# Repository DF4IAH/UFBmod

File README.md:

# UFBmod
Ultra-Fine-Business Modulation - Trying a new data modulation to compete with LoRa (R)

## Topics
UFMmod is intented to be a digital Spread Spectrum Modulation for data transfer with Low Power and High Range performance. It is non-chirp based, instead it uses Pseudo-Noise coding sequence.

## The frequencies to be used by UFMmod

### Europe
* 868 MHz ISM band (125 kHz bandwidth).
* 433 MHz band (3 kHz bandwidth).

### USA, Australia, Asia, Africa, Pacific region ...
* sorry, not defined yet.

## Directory structure

### DOCS
* Ideas and concepts of the modulation and realization for an data packet transceiver.
* Datasheets of the used parts.

### HW
* CAD/Eagle schematics and PCB layout
* Libraries
* CAM files

### FPGA
* XILINX Artix-7 configuration files with its Verilog source code.

### SW
* Software used by the FPGA internal soft processor. (not yet defined)
* Software used by an STM32L4xx MCU. (not yet defined)

<EOF>

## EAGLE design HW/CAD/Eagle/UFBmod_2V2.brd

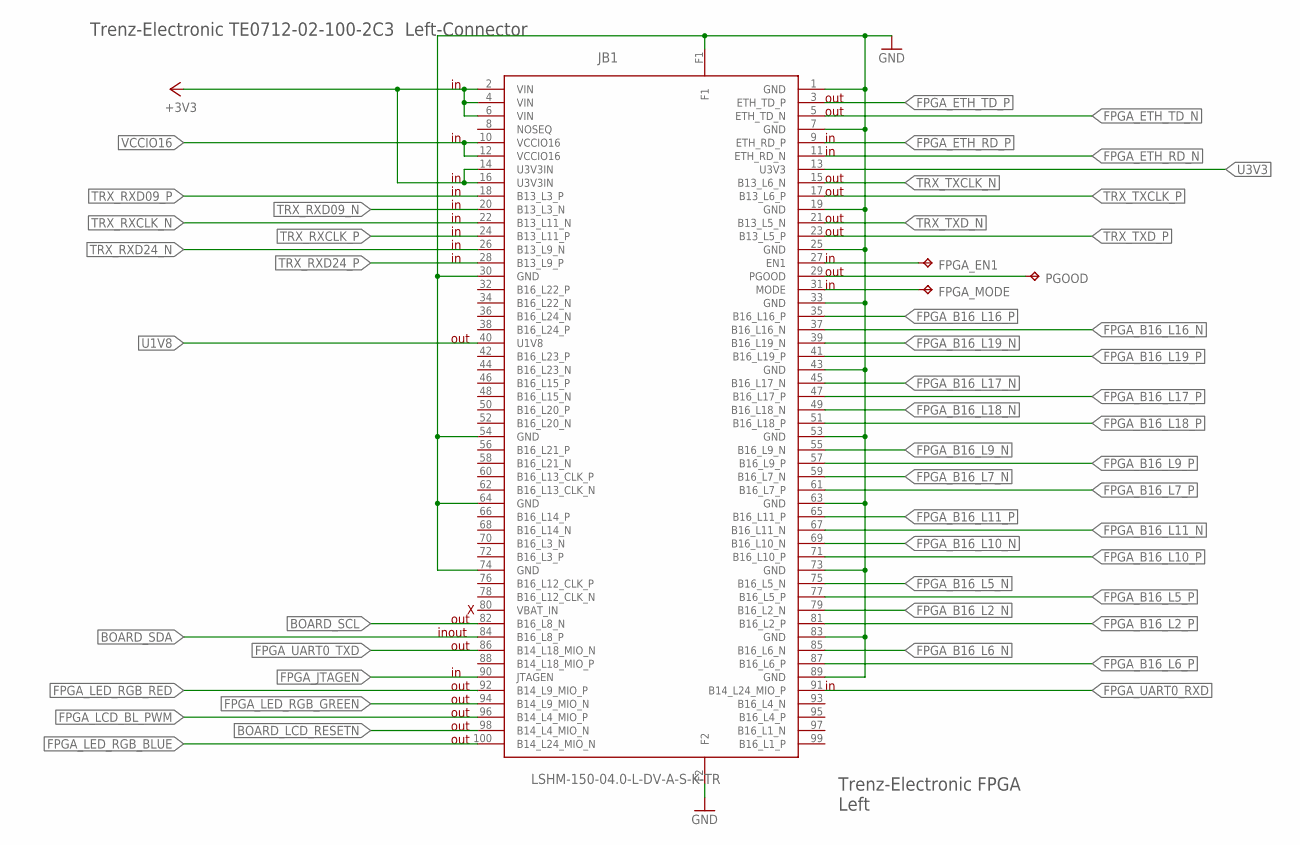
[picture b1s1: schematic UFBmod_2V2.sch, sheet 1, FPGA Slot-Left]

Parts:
FPGA_EN1: TPB1,27; B1,27
FPGA_MODE: TPB1,27; B1,27
JB1: LSHM-150-04.0-L-DV-A-S-K-TR; SAMTEC_LSHM-150-DV
PGOOD: TPB1,27; B1,27

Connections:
+3V3: JB1.2 (VIN), JB1.4 (VIN), JB1.6 (VIN), JB1.14 (U3V3IN), JB1.16 (U3V3IN); also elsewhere on the board
BOARD_LCD_RESETN: JB1.98 (B14_L4_MIO_N); also elsewhere on the board
BOARD_SCL: JB1.82 (B16_L8_N); also elsewhere on the board
BOARD_SDA: JB1.84 (B16_L8_P); also elsewhere on the board
FPGA_B16_L2_N: JB1.79 (B16_L2_N)
FPGA_B16_L2_P: JB1.81 (B16_L2_P)
FPGA_B16_L5_N: JB1.75 (B16_L5_N)
FPGA_B16_L5_P: JB1.77 (B16_L5_P)
FPGA_B16_L6_N: JB1.85 (B16_L6_N)
FPGA_B16_L6_P: JB1.87 (B16_L6_P)
FPGA_B16_L7_N: JB1.59 (B16_L7_N); also elsewhere on the board
FPGA_B16_L7_P: JB1.61 (B16_L7_P); also elsewhere on the board
FPGA_B16_L9_N: JB1.55 (B16_L9_N); also elsewhere on the board
FPGA_B16_L9_P: JB1.57 (B16_L9_P); also elsewhere on the board
FPGA_B16_L10_N: JB1.69 (B16_L10_N)
FPGA_B16_L10_P: JB1.71 (B16_L10_P)
FPGA_B16_L11_N: JB1.67 (B16_L11_N); also elsewhere on the board
FPGA_B16_L11_P: JB1.65 (B16_L11_P); also elsewhere on the board
FPGA_B16_L16_N: JB1.37 (B16_L16_N); also elsewhere on the board
FPGA_B16_L16_P: JB1.35 (B16_L16_P); also elsewhere on the board
FPGA_B16_L17_N: JB1.45 (B16_L17_N); also elsewhere on the board
FPGA_B16_L17_P: JB1.47 (B16_L17_P); also elsewhere on the board
FPGA_B16_L18_N: JB1.49 (B16_L18_N); also elsewhere on the board
FPGA_B16_L18_P: JB1.51 (B16_L18_P); also elsewhere on the board
FPGA_B16_L19_N: JB1.39 (B16_L19_N); also elsewhere on the board
FPGA_B16_L19_P: JB1.41 (B16_L19_P); also elsewhere on the board
FPGA_EN1: FPGA_EN1.TP, JB1.27 (EN1)
FPGA_ETH_RD_N: JB1.11 (ETH_RD_N); also elsewhere on the board
FPGA_ETH_RD_P: JB1.9 (ETH_RD_P); also elsewhere on the board
FPGA_ETH_TD_N: JB1.5 (ETH_TD_N); also elsewhere on the board
FPGA_ETH_TD_P: JB1.3 (ETH_TD_P); also elsewhere on the board
FPGA_JTAGEN: JB1.90 (JTAGEN); also elsewhere on the board
FPGA_LCD_BL_PWM: JB1.96 (B14_L4_MIO_P); also elsewhere on the board
FPGA_LED_RGB_BLUE: JB1.100 (B14_L24_MIO_N); also elsewhere on the board
FPGA_LED_RGB_GREEN: JB1.94 (B14_L9_MIO_N); also elsewhere on the board
FPGA_LED_RGB_RED: JB1.92 (B14_L9_MIO_P); also elsewhere on the board
FPGA_MODE: FPGA_MODE.TP, JB1.31 (MODE)
FPGA_UART0_RXD: JB1.91 (B14_L24_MIO_P); also elsewhere on the board
FPGA_UART0_TXD: JB1.86 (B14_L18_MIO_N); also elsewhere on the board
GND: JB1.1 (GND), JB1.7 (GND), JB1.19 (GND), JB1.25 (GND), JB1.30 (GND), JB1.33 (GND), JB1.43 (GND), JB1.53 (GND), JB1.54 (GND), JB1.63 (GND), JB1.64 (GND), JB1.73 (GND), JB1.74 (GND), JB1.83 (GND), JB1.89 (GND), JB1.F1, JB1.F2; also elsewhere on the board
PGOOD: JB1.29 (PGOOD), PGOOD.TP
TRX_RXCLK_N: JB1.22 (B13_L11_N); also elsewhere on the board
TRX_RXCLK_P: JB1.24 (B13_L11_P); also elsewhere on the board
TRX_RXD09_N: JB1.20 (B13_L3_N); also elsewhere on the board
TRX_RXD09_P: JB1.18 (B13_L3_P); also elsewhere on the board
TRX_RXD24_N: JB1.26 (B13_L9_N); also elsewhere on the board
TRX_RXD24_P: JB1.28 (B13_L9_P); also elsewhere on the board
TRX_TXCLK_N: JB1.15 (B13_L6_N); also elsewhere on the board
TRX_TXCLK_P: JB1.17 (B13_L6_P); also elsewhere on the board
TRX_TXD_N: JB1.21 (B13_L5_N); also elsewhere on the board
TRX_TXD_P: JB1.23 (B13_L5_P); also elsewhere on the board
U1V8: JB1.40 (U1V8); also elsewhere on the board
U3V3: JB1.13 (U3V3); also elsewhere on the board
VBAT_IN: JB1.80 (VBAT_IN)
VCCIO16: JB1.10 (VCCIO16), JB1.12 (VCCIO16); also elsewhere on the board

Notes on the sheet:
Trenz-Electronic FPGA Left
Trenz-Electronic TE0712-02-100-2C3 Left-Connector
out
inout

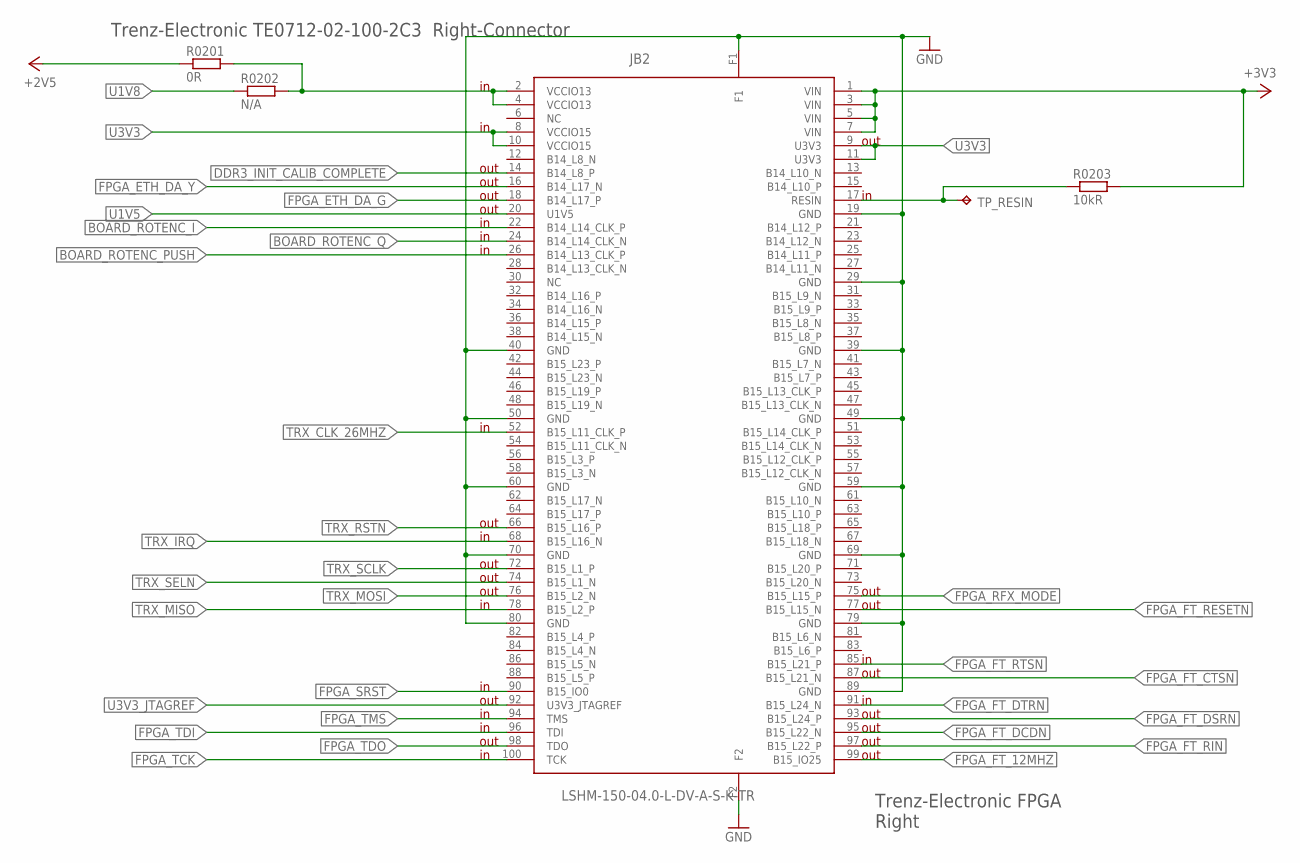
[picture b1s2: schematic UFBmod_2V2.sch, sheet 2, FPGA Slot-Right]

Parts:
JB2: LSHM-150-04.0-L-DV-A-S-K-TR; SAMTEC_LSHM-150-DV
R0201: 0R; R0402
R0202: N/A; R0402
R0203: 10kR; R0402
TP_RESIN: TPB1,27; B1,27

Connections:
+2V5: R0201.1; also elsewhere on the board
+3V3: JB2.1 (VIN), JB2.3 (VIN), JB2.5 (VIN), JB2.7 (VIN), R0203.2; also elsewhere on the board
BOARD_ROTENC_I: JB2.22 (B14_L14_CLK_P); also elsewhere on the board
BOARD_ROTENC_PUSH: JB2.26 (B14_L13_CLK_P); also elsewhere on the board
BOARD_ROTENC_Q: JB2.24 (B14_L14_CLK_N); also elsewhere on the board
DDR3_INIT_CALIB_COMPLETE: JB2.14 (B14_L8_P); also elsewhere on the board
FPGA_ETH_DA_G: JB2.18 (B14_L17_P); also elsewhere on the board
FPGA_ETH_DA_Y: JB2.16 (B14_L17_N); also elsewhere on the board
FPGA_FT_12MHZ: JB2.99 (B15_IO25); also elsewhere on the board
FPGA_FT_CTSN: JB2.87 (B15_L21_N); also elsewhere on the board
FPGA_FT_DCDN: JB2.95 (B15_L22_N); also elsewhere on the board
FPGA_FT_DSRN: JB2.93 (B15_L24_P); also elsewhere on the board
FPGA_FT_DTRN: JB2.91 (B15_L24_N); also elsewhere on the board
FPGA_FT_RESETN: JB2.77 (B15_L15_N); also elsewhere on the board
FPGA_FT_RIN: JB2.97 (B15_L22_P); also elsewhere on the board
FPGA_FT_RTSN: JB2.85 (B15_L21_P); also elsewhere on the board
FPGA_RFX_MODE: JB2.75 (B15_L15_P); also elsewhere on the board
FPGA_SRST: JB2.90 (B15_IO0); also elsewhere on the board
FPGA_TCK: JB2.100 (TCK); also elsewhere on the board
FPGA_TDI: JB2.96 (TDI); also elsewhere on the board
FPGA_TDO: JB2.98 (TDO); also elsewhere on the board
FPGA_TMS: JB2.94 (TMS); also elsewhere on the board
GND: JB2.19 (GND), JB2.29 (GND), JB2.39 (GND), JB2.40 (GND), JB2.49 (GND), JB2.50 (GND), JB2.59 (GND), JB2.60 (GND), JB2.69 (GND), JB2.70 (GND), JB2.79 (GND), JB2.80 (GND), JB2.89 (GND), JB2.F1, JB2.F2; also elsewhere on the board
RESIN: JB2.17 (RESIN), R0203.1, TP_RESIN.TP
TRX_CLK_26MHZ: JB2.52 (B15_L11_CLK_P); also elsewhere on the board
TRX_IRQ: JB2.68 (B15_L16_N); also elsewhere on the board
TRX_MISO: JB2.78 (B15_L2_P); also elsewhere on the board
TRX_MOSI: JB2.76 (B15_L2_N); also elsewhere on the board
TRX_RSTN: JB2.66 (B15_L16_P); also elsewhere on the board
TRX_SCLK: JB2.72 (B15_L1_P); also elsewhere on the board
TRX_SELN: JB2.74 (B15_L1_N); also elsewhere on the board
U1V5: JB2.20 (U1V5)
U1V8: R0202.1; also elsewhere on the board
U3V3: JB2.8 (VCCIO15), JB2.9 (U3V3), JB2.10 (VCCIO15), JB2.11 (U3V3); also elsewhere on the board
U3V3_JTAGREF: JB2.92 (U3V3_JTAGREF); also elsewhere on the board
VCCIO13: JB2.2 (VCCIO13), JB2.4 (VCCIO13), R0201.2, R0202.2; also elsewhere on the board

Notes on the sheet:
Trenz-Electronic TE0712-02-100-2C3 Right-Connector
Trenz-Electronic FPGA Right
out

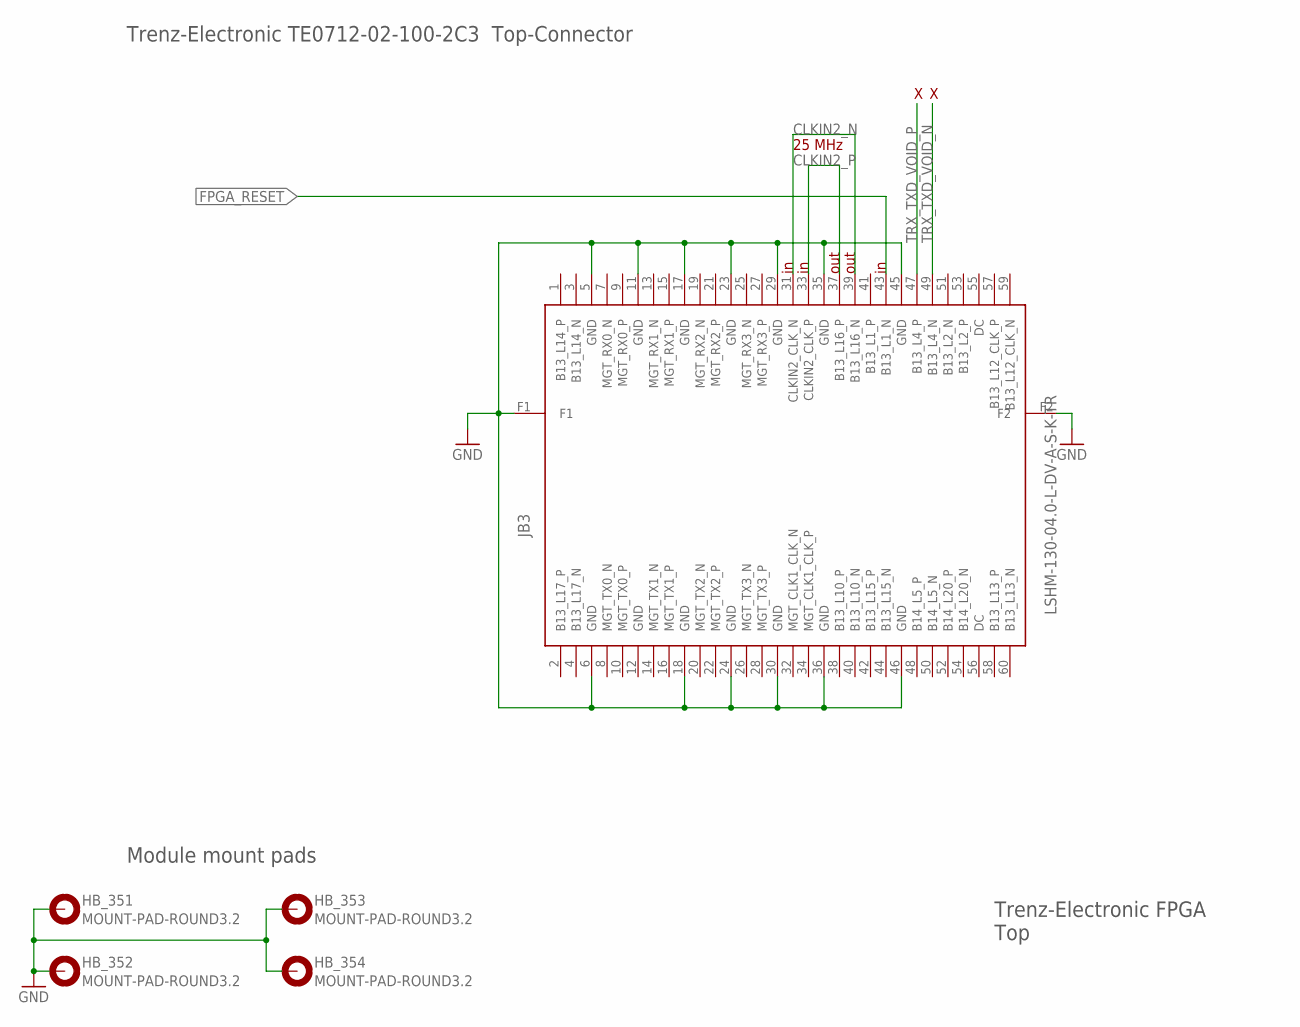
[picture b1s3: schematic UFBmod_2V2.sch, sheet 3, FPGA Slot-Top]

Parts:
HB_351, HB_352, HB_353, HB_354: MOUNT-PAD-ROUND3.2; 3,2-PAD
JB3: LSHM-130-04.0-L-DV-A-S-K-TR; SAMTEC_LSHM-130-DV

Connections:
CLKIN2_N: JB3.31 (CLKIN2_CLK_N), JB3.39 (B13_L16_N)
CLKIN2_P: JB3.33 (CLKIN2_CLK_P), JB3.37 (B13_L16_P)
FPGA_RESET: JB3.43 (B13_L1_N); also elsewhere on the board
GND: HB_351.B3,2, HB_352.B3,2, HB_353.B3,2, HB_354.B3,2, JB3.5 (GND), JB3.6 (GND), JB3.11 (GND), JB3.17 (GND), JB3.18 (GND), JB3.23 (GND), JB3.24 (GND), JB3.29 (GND), JB3.30 (GND), JB3.35 (GND), JB3.36 (GND), JB3.45 (GND), JB3.46 (GND), JB3.F1, JB3.F2; also elsewhere on the board
TRX_TXD_VOID_N: JB3.49 (B13_L4_N)
TRX_TXD_VOID_P: JB3.47 (B13_L4_P)

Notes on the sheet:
Trenz-Electronic TE0712-02-100-2C3 Top-Connector
Trenz-Electronic FPGA Top
Module mount pads
out
25 MHz

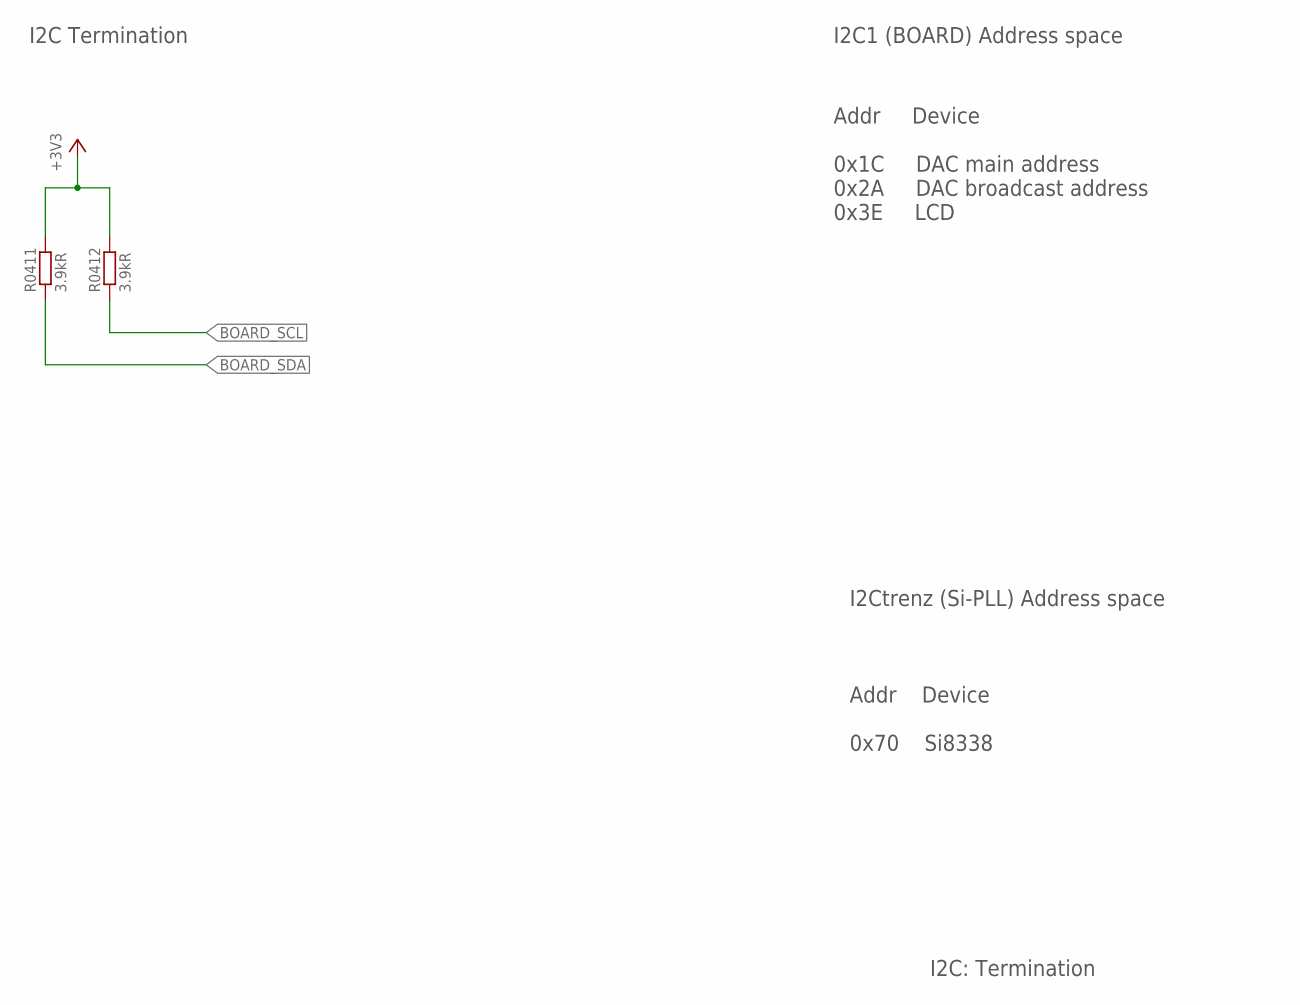
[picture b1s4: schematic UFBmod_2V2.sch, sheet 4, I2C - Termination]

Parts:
R0411, R0412: 3.9kR; R0402

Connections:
+3V3: R0411.2, R0412.2; also elsewhere on the board
BOARD_SCL: R0412.1; also elsewhere on the board
BOARD_SDA: R0411.1; also elsewhere on the board

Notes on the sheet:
I2C: Termination
I2C Termination
Addr Device 0x1C DAC main address 0x2A DAC broadcast address 0x3E LCD
I2C1 (BOARD) Address space
I2Ctrenz (Si-PLL) Address space
Addr Device 0x70 Si8338

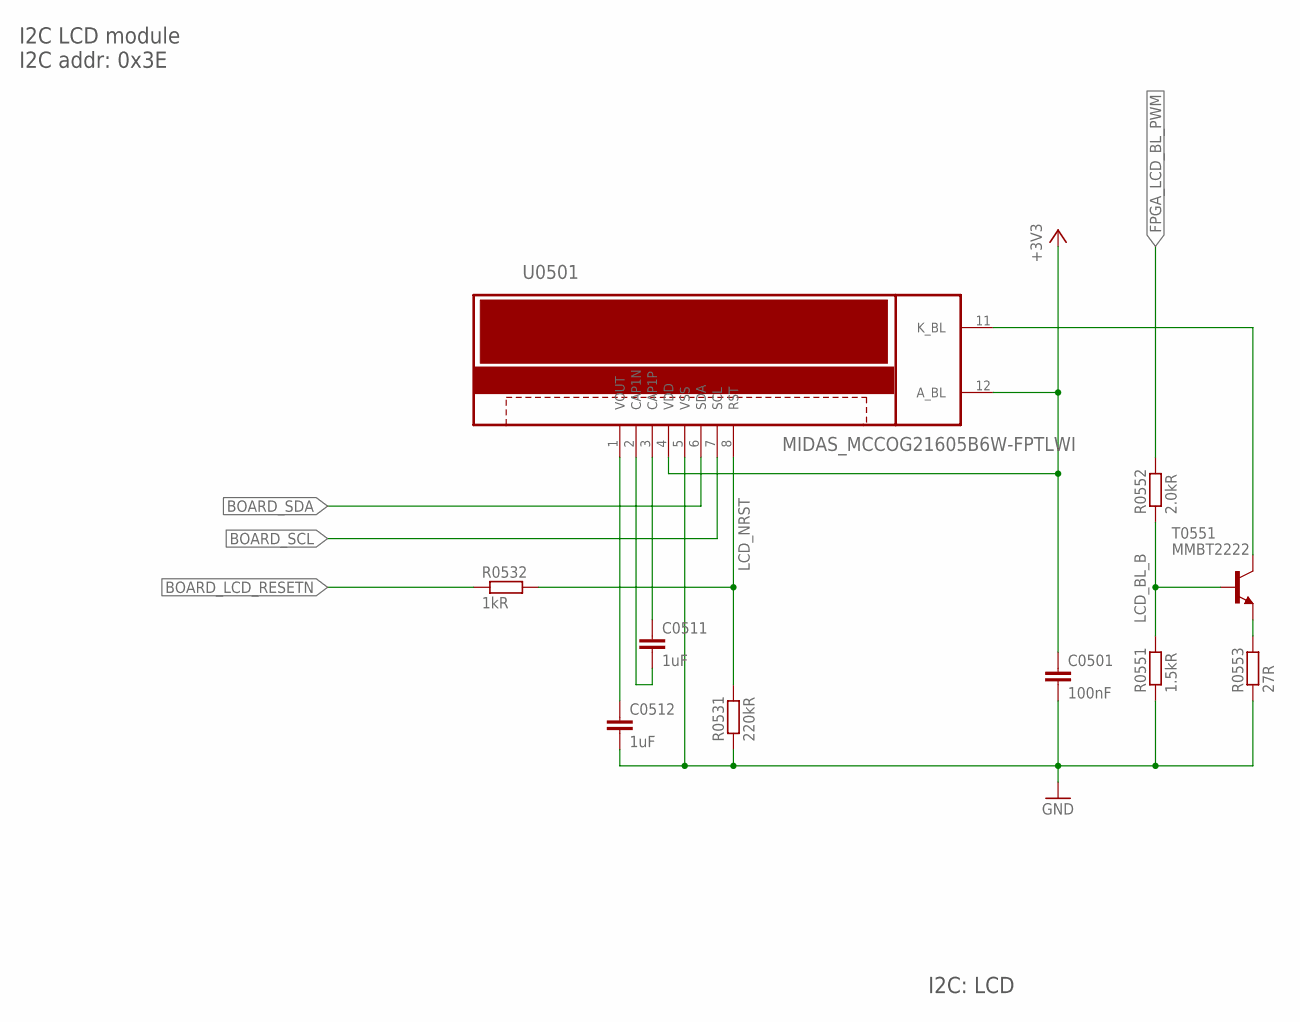
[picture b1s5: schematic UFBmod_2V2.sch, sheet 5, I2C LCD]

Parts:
C0501: 100nF; C0402
C0511, C0512: 1uF; C0402
R0531: 220kR; R0402
R0532: 1kR; R0402
R0551: 1.5kR; R0402
R0552: 2.0kR; R0402
R0553: 27R; R0603
T0551: MMBT2222; SOT23
U0501: MIDAS_MCCOG21605B6W-FPTLWI

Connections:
+3V3: C0501.1, U0501.4 (VDD), U0501.12 (A_BL); also elsewhere on the board
BOARD_LCD_RESETN: R0532.1; also elsewhere on the board
BOARD_SCL: U0501.7 (SCL); also elsewhere on the board
BOARD_SDA: U0501.6 (SDA); also elsewhere on the board
FPGA_LCD_BL_PWM: R0552.2; also elsewhere on the board
GND: C0501.2, C0512.2, R0531.1, R0551.1, R0553.1, U0501.5 (VSS); also elsewhere on the board
LCD_BL_B: R0551.2, R0552.1, T0551.1 (B)
LCD_BL_K: T0551.3 (C), U0501.11 (K_BL)
LCD_CAP1N: C0511.2, U0501.2 (CAP1N)
LCD_CAP1P: C0511.1, U0501.3 (CAP1P)
LCD_NRST: R0531.2, R0532.2, U0501.8 (RST)
LCD_VOUT: C0512.1, U0501.1 (VOUT)
LED_B_E: R0553.2, T0551.2 (E)

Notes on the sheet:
I2C LCD module I2C addr: 0x3E
I2C: LCD

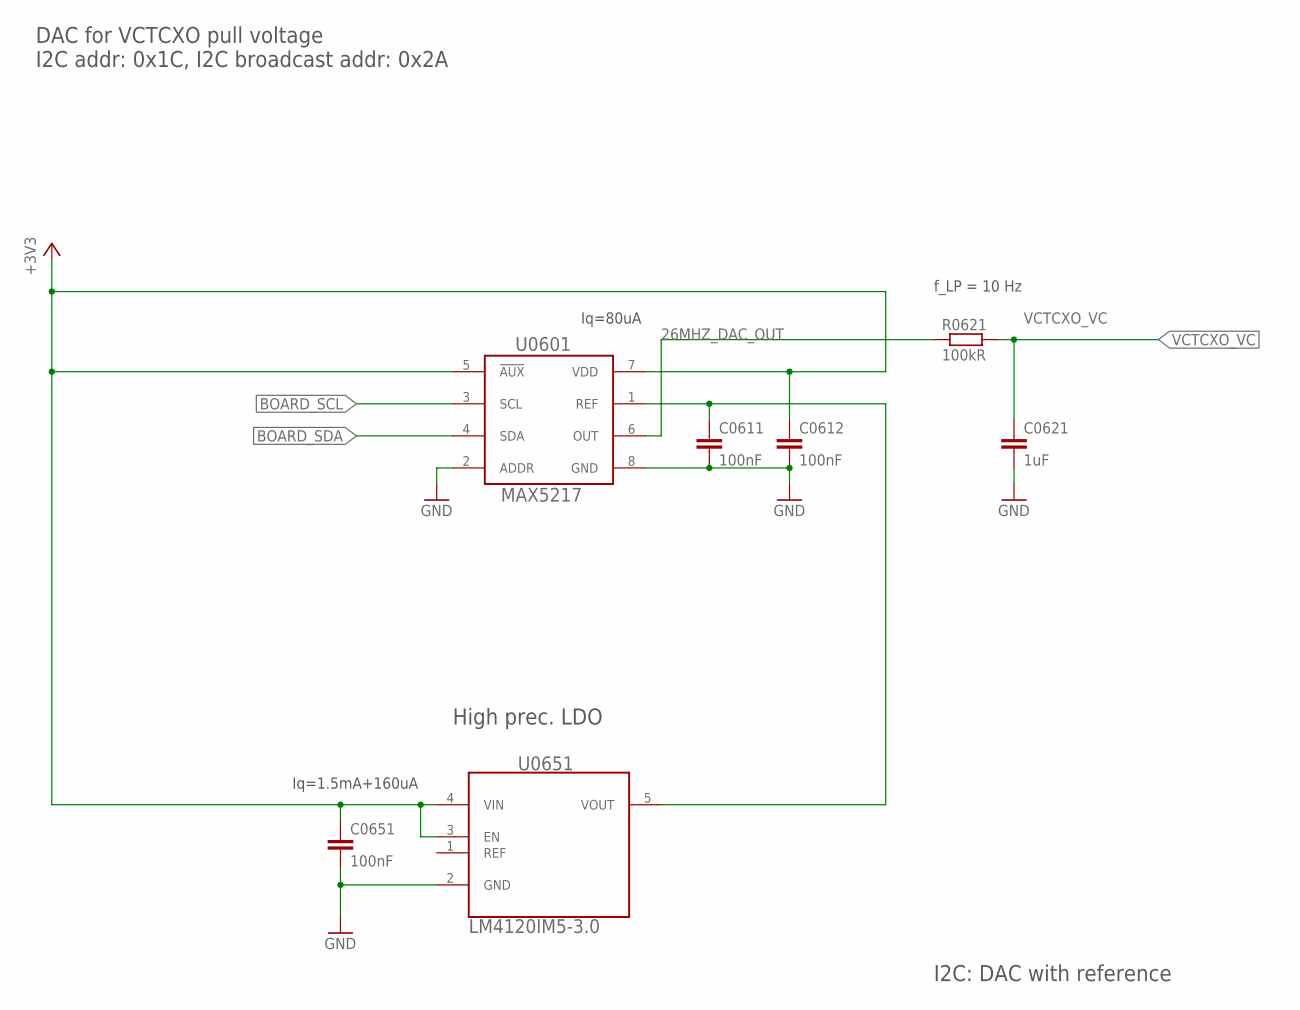
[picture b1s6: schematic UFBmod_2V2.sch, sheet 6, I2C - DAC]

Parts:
C0611, C0612, C0651: 100nF; C0402
C0621: 1uF; C0402
R0621: 100kR; R0402
U0601: MAX5217; µMAX8
U0651: LM4120IM5-3.0; SOT95P285X120-5N

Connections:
26MHZ_DAC_OUT: R0621.1, U0601.6 (OUT)
+3V0_20MHZ_VCTCXO: C0611.1, U0601.1 (REF), U0651.5 (VOUT)
+3V3: C0612.1, C0651.1, U0601.5 (!AUX), U0601.7 (VDD), U0651.3 (EN), U0651.4 (VIN); also elsewhere on the board
BOARD_SCL: U0601.3 (SCL); also elsewhere on the board
BOARD_SDA: U0601.4 (SDA); also elsewhere on the board
GND: C0611.2, C0612.2, C0621.2, C0651.2, U0601.2 (ADDR), U0601.8 (GND), U0651.2 (GND); also elsewhere on the board
VCTCXO_VC: C0621.1, R0621.2; also elsewhere on the board

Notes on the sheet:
f_LP = 10 Hz
Iq=80uA
DAC for VCTCXO pull voltage I2C addr: 0x1C, I2C broadcast addr: 0x2A
I2C: DAC with reference
High prec. LDO
Iq=1.5mA+160uA

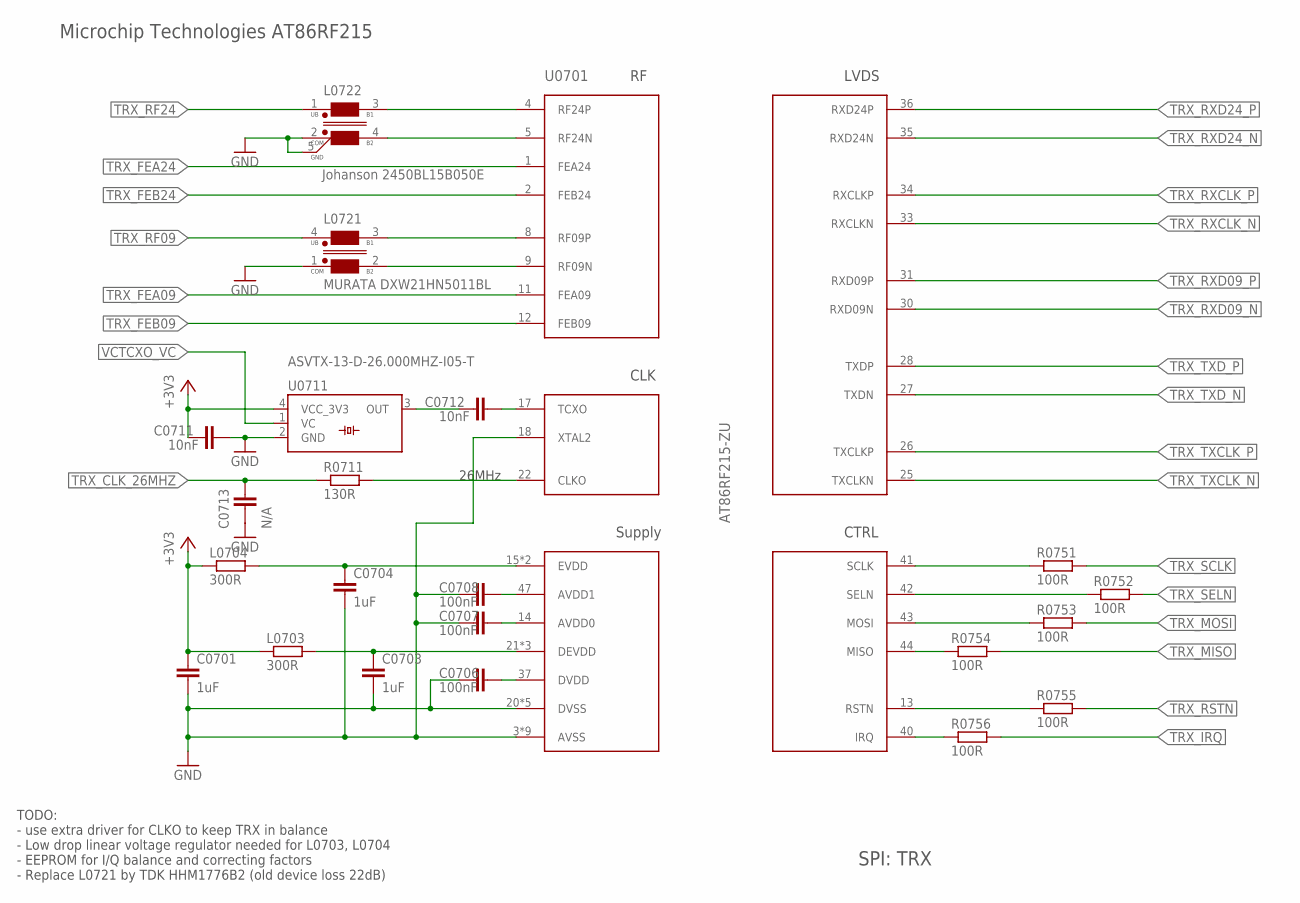
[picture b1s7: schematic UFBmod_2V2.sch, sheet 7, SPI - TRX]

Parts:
C0701, C0703, C0704: 1uF; C0402
C0706, C0707, C0708: 100nF; C0402
C0711, C0712: 10nF; C0402
C0713: N/A; C0402
L0703, L0704: 300R; R1206
L0721: MURATA DXW21HN5011BL; DXW21HN5011BL
L0722: Johanson 2450BL15B050E; 2450BL15B050
R0711: 130R; R0402
R0751, R0752, R0753, R0754, R0755, R0756: 100R; R0402
U0701: AT86RF215-ZU; QFN48_7X7-0P5-PAD
U0711: ASVTX-13-D-26.000MHZ-I05-T; ASVTX-13

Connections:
+3V3: C0701.1, C0711.1, L0703.1, L0704.1, U0711.4 (VCC_3V3); also elsewhere on the board
GND: C0701.2, C0703.2, C0704.2, C0706.1, C0707.1, C0708.1, C0711.2, C0713.1, L0721.1 (COM), L0722.2 (COM), L0722.5 (G_N_D), U0701.3 (AVSS), U0701.6 (AVSS), U0701.7 (AVSS), U0701.10 (AVSS), U0701.16 (AVSS), U0701.18 (XTAL2), U0701.19 (AVSS), U0701.20 (DVSS), U0701.23 (DVSS), U0701.24 (DVSS), U0701.32 (DVSS), U0701.38 (DVSS), U0701.45 (AVSS), U0701.48 (AVSS), U0701.49 (AVSS), U0711.2 (GND); also elsewhere on the board
TRX_AVDD0: C0707.2, U0701.14 (AVDD0)
TRX_AVDD1: C0708.2, U0701.47 (AVDD1)
TRX_CLKO_26MHZ_R: R0711.2, U0701.22 (CLKO)
TRX_CLK_26MHZ: C0713.2, R0711.1; also elsewhere on the board
TRX_DEVDD: C0703.1, L0703.2, U0701.21 (DEVDD), U0701.29 (DEVDD), U0701.39 (DEVDD)
TRX_DVDD: C0706.2, U0701.37 (DVDD)
TRX_EVDD: C0704.1, L0704.2, U0701.15 (EVDD), U0701.46 (EVDD)
TRX_FEA09: U0701.11 (FEA09); also elsewhere on the board
TRX_FEA24: U0701.1 (FEA24)
TRX_FEB09: U0701.12 (FEB09); also elsewhere on the board
TRX_FEB24: U0701.2 (FEB24)
TRX_IRQ: R0756.2; also elsewhere on the board
TRX_IRQ_R: R0756.1, U0701.40 (IRQ)
TRX_MISO: R0754.2; also elsewhere on the board
TRX_MISO_R: R0754.1, U0701.44 (MISO)
TRX_MOSI: R0753.2; also elsewhere on the board
TRX_MOSI_R: R0753.1, U0701.43 (MOSI)
TRX_RF09: L0721.4 (UB); also elsewhere on the board
TRX_RF09_N: L0721.2 (B2), U0701.9 (RF09N)
TRX_RF09_P: L0721.3 (B1), U0701.8 (RF09P)
TRX_RF24: L0722.1 (UB); also elsewhere on the board
TRX_RF24_N: L0722.4 (B2), U0701.5 (RF24N)
TRX_RF24_P: L0722.3 (B1), U0701.4 (RF24P)
TRX_RSTN: R0755.2; also elsewhere on the board
TRX_RSTN_R: R0755.1, U0701.13 (RSTN)
TRX_RXCLK_N: U0701.33 (RXCLKN); also elsewhere on the board
TRX_RXCLK_P: U0701.34 (RXCLKP); also elsewhere on the board
TRX_RXD09_N: U0701.30 (RXD09N); also elsewhere on the board
TRX_RXD09_P: U0701.31 (RXD09P); also elsewhere on the board
TRX_RXD24_N: U0701.35 (RXD24N); also elsewhere on the board
TRX_RXD24_P: U0701.36 (RXD24P); also elsewhere on the board
TRX_SCLK: R0751.2; also elsewhere on the board
TRX_SCLK_R: R0751.1, U0701.41 (SCLK)
TRX_SELN: R0752.2; also elsewhere on the board
TRX_SELN_R: R0752.1, U0701.42 (SELN)
TRX_TCXO: C0712.2, U0701.17 (TCXO)
TRX_TXCLK_N: U0701.25 (TXCLKN); also elsewhere on the board
TRX_TXCLK_P: U0701.26 (TXCLKP); also elsewhere on the board
TRX_TXD_N: U0701.27 (TXDN); also elsewhere on the board
TRX_TXD_P: U0701.28 (TXDP); also elsewhere on the board
VCTCXO_OUT: C0712.1, U0711.3 (OUT)
VCTCXO_VC: U0711.1 (VC); also elsewhere on the board

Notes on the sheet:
SPI: TRX
Microchip Technologies AT86RF215
26MHz
TODO: - use extra driver for CLKO to keep TRX in balance - Low drop linear voltage regulator needed for L0703, L0704 - EEPROM for I/Q balance and correcting factors - Replace L0721 by TDK HHM1776B2 (old device loss 22dB)

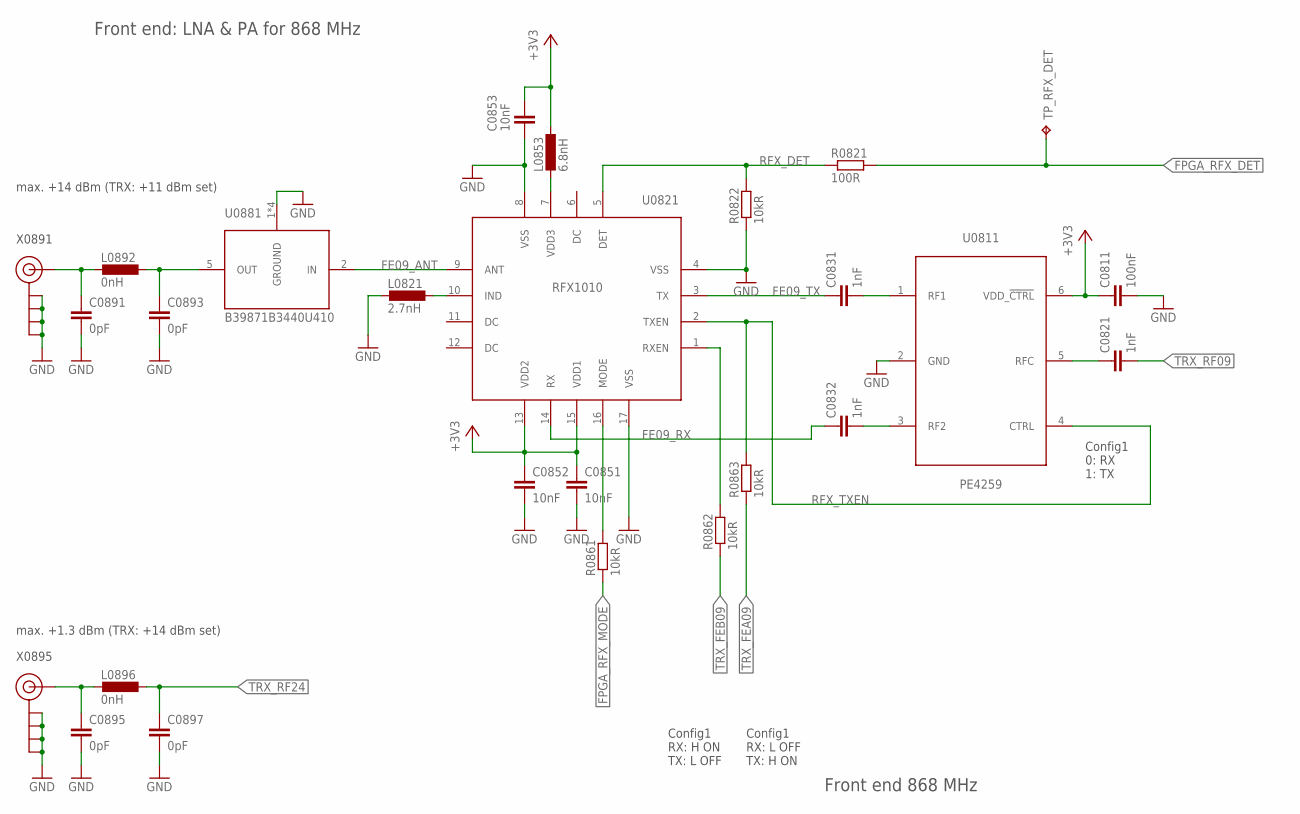
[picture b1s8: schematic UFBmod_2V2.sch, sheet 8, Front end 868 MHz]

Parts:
C0811: 100nF; C0402
C0821, C0831, C0832: 1nF; C0402
C0851, C0852, C0853: 10nF; C0402
C0891, C0893, C0895, C0897: 0pF; C0402
L0821: 2.7nH; L0603
L0853: 6.8nH; L0603
L0892, L0896: 0nH; L0603
R0821: 100R; R0402
R0822, R0861, R0862, R0863: 10kR; R0402
TP_RFX_DET: TPB1,27; B1,27
U0811: PE4259; SC-70_6-LEAD_2X1MM25_0P65
U0821: RFX1010; QFN16-3X3-0P5-PAD
U0881: B39871B3440U410; B3440_3MM-X-3MM
X0891, X0895: ANTENNATINY; SMA_UFL_PAD_TINY

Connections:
+3V3: C0811.1, C0851.1, C0852.1, C0853.1, L0853.1, U0811.6 (VDD_!CTRL), U0821.13 (VDD2), U0821.15 (VDD1); also elsewhere on the board
ANT09: C0891.1, L0892.2, X0891.ANT1 (SIGNAL), X0891.ANT2 (SIGNAL), X0891.ANT3 (SIGNAL)
ANT09_MATCH: C0893.1, L0892.1, U0881.5 (OUT)
ANT24: C0895.1, L0896.2, X0895.ANT1 (SIGNAL), X0895.ANT2 (SIGNAL), X0895.ANT3 (SIGNAL)
FE09_ANT: U0821.9 (ANT), U0881.2 (IN)
FE09_RX: C0832.1, U0821.14 (RX)
FE09_TX: C0831.1, U0821.3 (TX)
FPGA_RFX_DET: R0821.2, TP_RFX_DET.TP
FPGA_RFX_MODE: R0861.1; also elsewhere on the board
GND: C0811.2, C0851.2, C0852.2, C0853.2, C0891.2, C0893.2, C0895.2, C0897.2, L0821.2, R0822.1, U0811.2 (GND), U0821.4 (VSS), U0821.8 (VSS), U0821.17 (VSS), U0881.1 (GROUND), U0881.3 (GROUND), U0881.4 (GROUND), U0881.6 (GROUND), X0891.GND1 (GND), X0891.GND2 (GND), X0891.GND3 (GND), X0891.GND4 (GND), X0895.GND1 (GND), X0895.GND2 (GND), X0895.GND3 (GND), X0895.GND4 (GND); also elsewhere on the board
PE09_RF1: C0831.2, U0811.1 (RF1)
PE09_RF2: C0832.2, U0811.3 (RF2)
PE09_RFC: C0821.1, U0811.5 (RFC)
RFX_DET: R0821.1, R0822.2, U0821.5 (DET)
RFX_IND: L0821.1, U0821.10 (IND)
RFX_MODE: R0861.2, U0821.16 (MODE)
RFX_RXEN: R0862.2, U0821.1 (RXEN)
RFX_TXEN: R0863.2, U0811.4 (CTRL), U0821.2 (TXEN)
RFX_VDD3: L0853.2, U0821.7 (VDD3)
TRX_FEA09: R0863.1; also elsewhere on the board
TRX_FEB09: R0862.1; also elsewhere on the board
TRX_RF09: C0821.2; also elsewhere on the board
TRX_RF24: C0897.1, L0896.1; also elsewhere on the board

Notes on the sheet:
Front end: LNA & PA for 868 MHz
Front end 868 MHz
Config1 0: RX 1: TX
Config1 RX: H ON TX: L OFF
Config1 RX: L OFF TX: H ON
X0891
X0895
max. +1.3 dBm (TRX: +14 dBm set)
max. +14 dBm (TRX: +11 dBm set)

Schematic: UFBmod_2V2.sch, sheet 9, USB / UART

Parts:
C0911, C0913, C0914, C0916, C0917, C0918, C0921, C0922: 100nF; C0402
C0912, C0923, C0924: 4.7uF; C0603
D0971: CMD17-21VGD/TR8 GREEN; CHIP-LED0805
D0972: CMD17-21VRD/TR8 RED; CHIP-LED0805
L0911, L0921, L0922: 300R; R1206
R0911: 12kR 1%0; R0402
R0912, R0941, R0961, R0962, R0963, R0964, R0965, R0966, R0967, R0968: 100R; R0402
R0913: 100kR; R0402
R0931, R0981: 10kR; R0402
R0971, R0972: 560R; R0402
R0991: N/A; R0402
TP_TXDEN: TPB1,27; B1,27
U0911: FT232HL; LQFP48

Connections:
+3V3: C0911.1, C0912.1, C0916.1, C0917.1, C0918.1, D0971.A, D0972.A, L0921.2, L0922.2, R0931.2, R0981.2, U0911.12 (VCCIO), U0911.24 (VCCIO), U0911.39 (VCCD), U0911.40 (VREGIN), U0911.46 (VCCIO); also elsewhere on the board
+5V_USB: R0991.1; also elsewhere on the board
FPGA_FT_12MHZ: R0941.1; also elsewhere on the board
FPGA_FT_CTSN: R0964.2; also elsewhere on the board
FPGA_FT_DCDN: R0967.2; also elsewhere on the board
FPGA_FT_DSRN: R0966.2; also elsewhere on the board
FPGA_FT_DTRN: R0965.2; also elsewhere on the board
FPGA_FT_RESETN: R0912.1; also elsewhere on the board
FPGA_FT_RIN: R0968.2; also elsewhere on the board
FPGA_FT_RTSN: R0963.2; also elsewhere on the board
FPGA_UART0_RXD: R0961.2; also elsewhere on the board
FPGA_UART0_TXD: R0962.2; also elsewhere on the board
FT_ACBUS7: R0991.2, U0911.31 (ACBUS7)
FT_AGND: L0911.2, U0911.4 (AGND), U0911.9 (AGND), U0911.41 (AGND)
FT_CTS: R0964.1, U0911.16 (ADBUS3)
FT_DCD: R0967.1, U0911.19 (ADBUS6)
FT_DSR: R0966.1, U0911.18 (ADBUS5)
FT_DTR: R0965.1, U0911.17 (ADBUS4)
FT_EEDATA: R0931.1, U0911.43 (EEDATA)
FT_OSCI: R0941.2, U0911.1 (OSCI)
FT_REF: R0911.2, U0911.5 (REF)
FT_RESET: R0912.2, R0913.2, U0911.34 (!RESET)
FT_RI: R0968.1, U0911.20 (ADBUS7)
FT_RTS: R0963.1, U0911.15 (ADBUS2)
FT_RXD: R0962.1, U0911.14 (ADBUS1)
FT_RXLED: R0971.1, U0911.27 (ACBUS3)
FT_RXLED_D: D0971.C, R0971.2
FT_TXD: R0961.1, U0911.13 (ADBUS0)
FT_TXDEN: R0981.1, TP_TXDEN.TP, U0911.21 (ACBUS0)
FT_TXLED: R0972.1, U0911.28 (ACBUS4)
FT_TXLED_D: D0972.C, R0972.2
FT_VCCA: C0914.2, U0911.37 (VCCA)
FT_VCORE: C0913.2, U0911.38 (VCCCORE)
FT_VPHY: C0922.2, C0924.1, L0922.1, U0911.3 (VPHY)
FT_VPLL: C0921.2, C0923.1, L0921.1, U0911.8 (VPLL)
GND: C0911.2, C0912.2, C0913.1, C0914.1, C0916.2, C0917.2, C0918.2, C0921.1, C0922.1, C0923.2, C0924.2, L0911.1, R0911.1, R0913.1, U0911.10 (GND), U0911.11 (GND), U0911.22 (GND), U0911.23 (GND), U0911.35 (GND), U0911.36 (GND), U0911.42 (TEST), U0911.47 (GND), U0911.48 (GND); also elsewhere on the board
USB_D_N: U0911.6 (D_M); also elsewhere on the board
USB_D_P: U0911.7 (D_P); also elsewhere on the board

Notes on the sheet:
USB / UART
USB / UART FT232H
out
Self-Powered Configuration Example 2
w/o EEPROM: bus powered mode (500 mA)

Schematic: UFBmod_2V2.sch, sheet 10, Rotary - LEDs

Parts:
C1011, C1012, C1013: 100nF; C0402
D1021: ASMT-YTB7-0AA02_RGB; ASMT-YTB7_0AA02_RGB
R1011, R1012, R1013, R1022: 1kR; R0402
R1021, R1023: 820R; R0402
X1011: TTE_EN11-HSM

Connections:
BOARD_ROTENC_I: R1011.2; also elsewhere on the board
BOARD_ROTENC_PUSH: R1013.2; also elsewhere on the board
BOARD_ROTENC_Q: R1012.2; also elsewhere on the board
FPGA_LED_RGB_BLUE: R1023.2; also elsewhere on the board
FPGA_LED_RGB_GREEN: R1022.2; also elsewhere on the board
FPGA_LED_RGB_RED: R1021.2; also elsewhere on the board
GND: C1011.2, C1012.2, C1013.2, D1021.1 (BC), D1021.2 (GC), D1021.3 (RC), X1011.C, X1011.D; also elsewhere on the board
LED_RGB_BLUE: D1021.6 (BA), R1023.1
LED_RGB_GREEN: D1021.5 (GA), R1022.1
LED_RGB_RED: D1021.4 (RA), R1021.1
ROT_I: C1011.1, R1011.1, X1011.A
ROT_P: C1013.1, R1013.1, X1011.E
ROT_Q: C1012.1, R1012.1, X1011.B

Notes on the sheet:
Rotary encoder
RGB LEDs
User Control
PULLUP in FPGA to be enabled !

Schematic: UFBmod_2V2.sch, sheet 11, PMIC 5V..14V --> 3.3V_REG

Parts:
C1101: 4.7uF; C0805
C1102: 1uF; C0402
C1108: 100nF; C0805
C1111, C1112, C1113, C1114: 22uF; C0805
C1122: N/A; C0805
C1131: 100nF; C0402
C1132: 1nF; C0402
C1151, C1152, C1153: 100uF; C0805
D1111, D1112, D1161: CRS08; SOD80C
L1101: 470nH; L5650M
R1101: 10kR 0%5; R0402
R1102: 45.3kR 0%5; R0402
R1103, R1104: N/A; R0402
R1105: 110kR; R0402
R1106: 200kR; R0402
R1107: 100kR; R0402
R1108: 2R; R0805
R1122: N/A; R0805
R1131: 15kR; R0402
R1161: 220kR; R0402
U1101: TPS53353; DQP-22

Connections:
+3V3: C1131.1, C1151.1, C1152.1, C1153.1, L1101.1, R1102.2, R1104.1; also elsewhere on the board
+5V_USB: D1112.A; also elsewhere on the board
GND: C1101.1, C1102.1, C1111.1, C1112.1, C1113.1, C1114.1, C1122.2, C1151.2, C1152.2, C1153.2, R1101.1, R1103.1, R1105.1, R1106.1, U1101.23 (VSS_PAD), U1101.24 (VSS_PAD), U1101.P$1 (VSS_PAD), U1101.P$2 (VSS_PAD), U1101.P$3 (VSS_PAD), U1101.P$4 (VSS_PAD), U1101.P$5 (VSS_PAD), U1101.P$6 (VSS_PAD), U1101.P$7 (VSS_PAD), U1101.P$8 (VSS_PAD), U1101.P$9 (VSS_PAD), U1101.P$10 (VSS_PAD), U1101.P$11 (VSS_PAD), U1101.P$12 (VSS_PAD), U1101.P$13 (VSS_PAD), U1101.P$14 (VSS_PAD), U1101.P$15 (VSS_PAD), U1101.P$16 (VSS_PAD), U1101.P$17 (VSS_PAD), U1101.P$18 (VSS_PAD), U1101.P$19 (VSS_PAD), U1101.P$20 (VSS_PAD), U1101.P$21 (VSS_PAD); also elsewhere on the board
TPS_COR: C1131.2, C1132.1, R1131.2
TPS_EN: D1161.A, R1161.1, U1101.2 (EN)
TPS_LL: C1108.1, L1101.2, R1122.2, R1131.1, U1101.6 (LL), U1101.7 (LL), U1101.8 (LL), U1101.9 (LL), U1101.10 (LL), U1101.11 (LL)
TPS_LL_RC: C1122.1, R1122.1
TPS_MODE: R1106.2, U1101.20 (MODE)
TPS_PGOOD: R1107.1, U1101.3 (PGOOD)
TPS_RF: R1103.2, R1104.2, U1101.22 (RF)
TPS_TRIP: R1105.2, U1101.21 (TRIP)
TPS_VBST: R1108.1, U1101.4 (VBST)
TPS_VBST_R: C1108.2, R1108.2
TPS_VFB: C1132.2, R1101.2, R1102.1, U1101.1 (VFB)
TPS_VIN: C1101.2, C1111.2, C1112.2, C1113.2, C1114.2, D1111.C, D1112.C, R1161.2, U1101.12 (VIN), U1101.13 (VIN), U1101.14 (VIN), U1101.15 (VIN), U1101.16 (VIN), U1101.17 (VIN), U1101.19 (VDD)
TPS_VREG: C1102.2, D1161.C, R1107.2, U1101.18 (VREG)
VIN_PWR: D1111.A; also elsewhere on the board

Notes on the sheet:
PMIC 5V..14V --> 3.3V_REG
PMIC: 5V..14V --> 3.3V
PULSE PA5003.471NLT (470 nH, 18.4 A, 4.13 mR) 5.50 mm x 5.30 mm
(Better: 1uH .. 1.5 uH)
25V
f=300kHz
0.6V
5V0 out
5V0 in

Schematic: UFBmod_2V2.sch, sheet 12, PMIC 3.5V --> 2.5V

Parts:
C1201, C1221: 10uF; C0603
L1211: 4.7uH; L2520
R1211: 10kR; R0402
U1211: TPS62745DSSR; WSON-12

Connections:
+2V5: C1221.1, L1211.1, U1211.5 (VOUT); also elsewhere on the board
+3V3: C1201.1, U1211.1 (VIN), U1211.9 (VSEL3), U1211.10 (VSEL2), U1211.11 (VSEL1); also elsewhere on the board
GND: C1201.2, C1221.2, U1211.3 (VSS), U1211.4 (EN_VIN_SW), U1211.8 (VSEL4), U1211.13 (VSS), U1211.14 (VSS), U1211.G1 (VSS), U1211.G2 (VSS), U1211.G3 (VSS); also elsewhere on the board
PMIC2V5_SW: L1211.2, U1211.2 (SW)
TPS2_EN: R1211.2, U1211.12 (EN)
U3V3: R1211.1; also elsewhere on the board

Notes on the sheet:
PMIC 3.5V --> 2.5V
PMIC: 3.5V --> 2.5V
MURATA DFE252010P-4R7M=P2 2.50 mm x 2.00 mm
Prog: 2.5V
300mA

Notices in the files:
HW/CAD/Eagle/UFBmod_1V1.brd:
(C) 2019
HW/CAD/Eagle/UFBmod_2V2.brd:
(C) 2021
